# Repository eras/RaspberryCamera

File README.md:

RaspberryCamera
===============

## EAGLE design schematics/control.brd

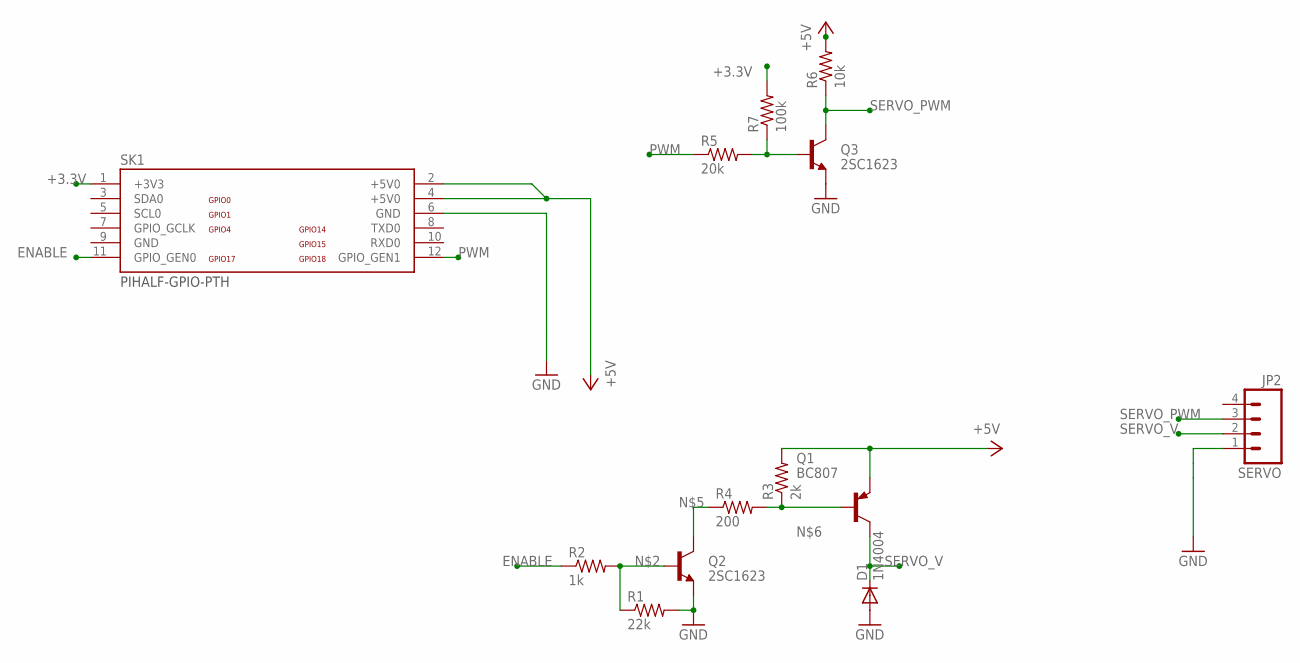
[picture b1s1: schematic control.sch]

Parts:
D1: 1N4004; SOD-323
JP2: SERVO; 1X04-SMD
Q1: BC807; SOT23-BCE
Q2, Q3: 2SC1623; SOT23
R1: 22k; M0805
R2: 1k; M0805
R3: 2k; M0805
R4: 200; M0805
R5: 20k; M0805
R6: 10k; M0805
R7: 100k; M0805
SK1: PIHALF-GPIO-PTH; GPIO-CONNECTOR-HALF

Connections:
+3.3V: R7.2, SK1.1 (+3V3)
+5V: Q1.E, R3.2, R6.2, SK1.2 (+5V0), SK1.4 (+5V0)
ENABLE: R2.1, SK1.11 (GPIO_GEN0)
GND: D1.2 (A), JP2.1, Q2.2 (E), Q3.2 (E), R1.2, SK1.6 (GND), SK1.9 (GND)
unnamed: Q3.1 (B), R5.2, R7.1
unnamed: Q2.1 (B), R1.1, R2.2
unnamed: Q2.3 (C), R4.1
unnamed: Q1.B, R3.1, R4.2
PWM: R5.1, SK1.12 (GPIO_GEN1)
SERVO_PWM: JP2.3, Q3.3 (C), R6.1
SERVO_V: D1.1 (C), JP2.2, Q1.C

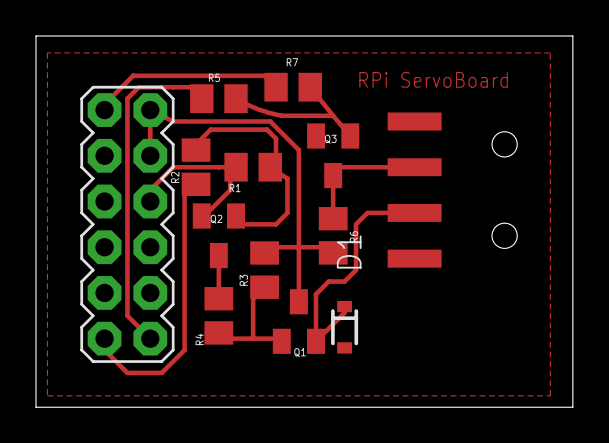
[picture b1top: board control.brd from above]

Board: 2 copper layers, 29.8 x 20.6 mm, 13 parts (0 on the bottom side), 11 nets.

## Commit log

2013-09-05 First stab of the board
2013-09-05 GnuCAP files
2013-09-06 LICENSE: updated author
2013-09-06 LICENSE: mention that some components are from Sparkfun Eagle Libraries
2013-09-06 LICENSE: {organization} -> author

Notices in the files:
parts and their libraries:
SparkFun: Licensing: CC v3.0 Share-Alike You are welcome to use this library for commercial purposes.
